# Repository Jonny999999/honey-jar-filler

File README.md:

# honey-jar-filler

Semi-automatic **weight-based honey jar filler** with a **jar carousel/magazine** and a
**servo-actuated honey gate**. A load cell weighs each jar in real time while the
firmware modulates the gate to hit a target fill mass.

This repository holds the complete build — **KiCad PCB**, **FreeCAD** mechanics, and
**ESP-IDF firmware** — plus the telemetry tooling used to capture and analyse fills.
The machine is also the subject of a **bachelor thesis** that evaluates several
**dosing strategies** for accurately dispensing a viscous, drifting medium (honey);
see [Dosing strategies](#dosing-strategies).

*System overview (CAD): pressurised bucket on the stand, the servo-actuated gate, and
the carousel base housing the control board and load cell, with a jar in position.*

*Left: the custom control board, fully populated. Right: I/O bring-up with all
peripherals connected.*

## Repo contents
- `pcb_honey-jar-filler/` — KiCad project (schematic, PCB, exports)
- `cad/` — FreeCAD parts, 3D models, full assembly
- `firmware_honey-jar-filler/` — ESP32 firmware (ESP-IDF)
- `tools/telemetry/` — host-side capture, run-splitting, and plotting tools
- `doc/` — build photos and notes

## Features (PCB / system)
- Load cell input (HX711) for weight-based dosing
- UI: rotary encoder, 2× buttons, LEDs, OLED display (I²C)
- Actuation: servo interface for honey gate; motor output for carousel
- Optional outputs: heater control, tank pressurization valve
- Power: 12–40 V input, 5 V buck (logic), adjustable 4–9 V rail (servo)

## Dosing strategies
Dosing honey accurately is hard: there is a **dead time** of several seconds between
moving the gate and seeing the weight respond, the flow **keeps dripping after the
gate closes**, the gate→flow relationship is **nonlinear**, and disturbances
(viscosity, temperature, falling bucket level) **drift within and between fills**.
Fixed thresholds therefore cannot stay optimal, which is what motivates the strategy
comparison at the heart of the thesis.

The firmware implements the strategies as interchangeable modules
(`firmware_honey-jar-filler/components/filler/`), selectable from the OLED menu:

- **heuristic** — fixed two-stage thresholds; the simple baseline.
- **adaptive-heuristic** — the same fill sequence, but dead time, post-close drip and
  fill rates are learned between fills, so it converges after a jar or two.
- **flow-cascade** — a control-based approach: an outer deceleration rate profile
  (feed-forward trajectory) feeding an inner PI rate loop with an online-identified
  affine plant model and Smith-predictor dead-time compensation.
- **manual** / **sequence** — encoder-driven and scripted modes, used for bring-up and
  for capturing clean reference runs.

## Roadmap / ideas
- Rotary carousel automation (indexing, run/stop with braking)
- Outlet warming (silicone band / water jacket)
- Jar presence detection
- Web UI / profiles / batch counter

## Schematic + layout preview
<p align="center">

</p>

## Firmware build (ESP-IDF)
- Install ESP-IDF **v5.5.1** and export its environment (`. ./export.sh`).
- Enter the firmware project:
```bash
cd firmware_honey-jar-filler
```
- Set the target and build:
```bash
idf.py set-target esp32
idf.py build
```
- No separate "install components" step is needed — `idf.py build` auto-fetches
  the managed components listed in `main/idf_component.yml` (esp-idf-lib hx711/
  encoder, ssd1306, servo, led_strip) into `managed_components/` on first run.
  `managed_components/` and `build/` are gitignored and regenerated per machine.
- `dependencies.lock` **is** committed and pins exact component versions — do
  not delete it. Some `idf_component.yml` entries use unbounded ranges (e.g.
  `esp-idf-lib/hx711: '*'`), and upstream has shipped breaking API changes
  under those ranges before (`esp-idf-lib/encoder` v2.0.0 rewrote the whole
  API); without the lock file, a fresh clone can silently resolve to an
  incompatible version and fail to compile.
- Flash and monitor (adjust serial port as needed):
```bash
idf.py -p /dev/ttyUSB0 flash monitor
```

## Firmware presets
- Runtime parameters are still defined centrally in `firmware_honey-jar-filler/components/app/app_params_def.h`.
- Each parameter there has one baseline default plus metadata such as min/max/step, UI text, and a scope:
  `APP_PARAM_SCOPE_PRESET` for recipe-specific values and `APP_PARAM_SCOPE_MACHINE` for shared machine settings.
- Built-in preset names and their default overrides live in `firmware_honey-jar-filler/components/app/app.c`.
  These preset defaults only override recipe-scoped fields; they do not duplicate the full parameter list.
- NVS stores shared machine settings separately from editable preset values:
  `machine_v1` for shared settings and `presets_v1` for preset-specific values.
- At boot, the active runtime config is rebuilt from baseline defaults + selected preset defaults + persisted machine settings + persisted preset values.

## Telemetry tools
- Structured telemetry is emitted on the normal UART console with a `TEL ` prefix and JSON payload.
- Normal ESP logs and machine telemetry therefore share one serial stream, but the telemetry lines can be split cleanly on the host.
- The intended workflow is:
  1. capture a session from UART
  2. keep the full console log for debugging
  3. store telemetry separately as NDJSON
  4. split runs and generate thesis figures from those files

Current script layout:
- `tools/telemetry/telemetry_tui.py`
  Recommended interactive wrapper / TUI entrypoint. Guides the user through
  capture, split, and plotting with session discovery, defaults, and command
  previews, while still calling the underlying scripts directly.
- `tools/telemetry/src/`
  Internal shared helpers for the telemetry scripts. Not intended to be run
  directly.
- `tools/telemetry/capture.py`
  Fully usable serial capture tool. Replaces the basic `idf.py monitor` workflow for experiment sessions and shows a live status line with telemetry counters.
- `tools/telemetry/split_runs.py`
  Offline splitter that converts one captured session into per-fill NDJSON files.
  It detects jar filling windows from `state=FILL`, adds configurable pre/post context,
  and writes `fills/index.json` plus `fill_0001.ndjson`, `fill_0002.ndjson`, ...
- `tools/telemetry/plot_runs.py`
  Offline chart exporter for thesis figures. It writes both a plain LaTeX-ready
  chart and a debug variant with metadata, based on fill mass, gate percentage,
  and FSM state overlays.
- `tools/telemetry/strategy_compare.py`
  Cross-strategy comparison charts (accuracy point clouds, speed–accuracy
  trade-off, throughput) for the thesis' strategy-comparison chapter. Reads each
  session's per-fill summaries and is explicit about which runs are a controlled
  comparison and which are only indicative.
- `tools/telemetry/cascade_analyze.py`
  Diagnostics for the flow-cascade strategy: per-fill plant-model estimate
  (gain/onset/lag) beside an offline ground-truth fit, to spot a diverging
  identifier at a glance.

Session capture output:
- `data/telemetry/<session>/session.log`
  Full serial console output, including normal ESP logs and raw `TEL` lines.
- `data/telemetry/<session>/telemetry.ndjson`
  Only telemetry payload lines, one JSON object per line.
- `data/telemetry/<session>/runs/run_0001.ndjson`
  Per-run telemetry files created live from `run_start` / `run_end` events, including configurable pre/post context.
- `data/telemetry/<session>/fills/index.json`
  Offline manifest of detected jar-fill windows with timing, preset, and parameter metadata.
- `data/telemetry/<session>/fills/fill_0001.ndjson`
  One offline per-fill telemetry slice intended for plotting and later comparison.
- `data/telemetry/<session>/session_meta.json`
  Port, baud rate, and capture timing settings.

Example capture usage:
```bash
python3 tools/telemetry/capture.py --port /dev/ttyUSB0 --baud 115200
```

Recommended interactive workflow:
```bash
python3 tools/telemetry/telemetry_tui.py
```

Example offline workflow:
```bash
python3 tools/telemetry/split_runs.py data/telemetry/2026.06.12_11:39-x-test --force
python3 tools/telemetry/plot_runs.py data/telemetry/2026.06.12_11:39-x-test/fills --list
python3 tools/telemetry/plot_runs.py data/telemetry/2026.06.12_11:39-x-test/fills --fills 1,3 --format pdf --format svg
```

Useful options:
- `--show-tel`
  Also print the `TEL` lines in the terminal instead of only saving them to files.
- `--pre-run-ms 2000 --post-run-ms 2000`
  Keep more telemetry context around each detected run.
- `--session-name my-test`
  Add a readable suffix after the timestamp, for example
  `2026.06.07_22:30-x-my-test`.

Goal of this tooling:
- keep experiment data self-describing and reproducible
- avoid manually filtering UART logs after each test
- support later batch plotting to vector PDF/SVG figures for the thesis
- preserve enough event context to compare different presets and control strategies cleanly
- make it obvious during capture that the custom telemetry tool is running, not plain `idf.py monitor`

## Wiring (servo mount DIN cable)
The cable with 15-pin DIN connector from the base assembly to the servo mount carries OLED, encoder, and servo signals + power.

OLED:
- green: GND
- red: 3V3
- orange: SDA
- yellow: SCL

Encoder:
- gray: SW
- blue: B
- light-green: A

Servo:
- brown, gray-brown, pink: 8V
- gray-black, black, white: GND
- purple: PWM

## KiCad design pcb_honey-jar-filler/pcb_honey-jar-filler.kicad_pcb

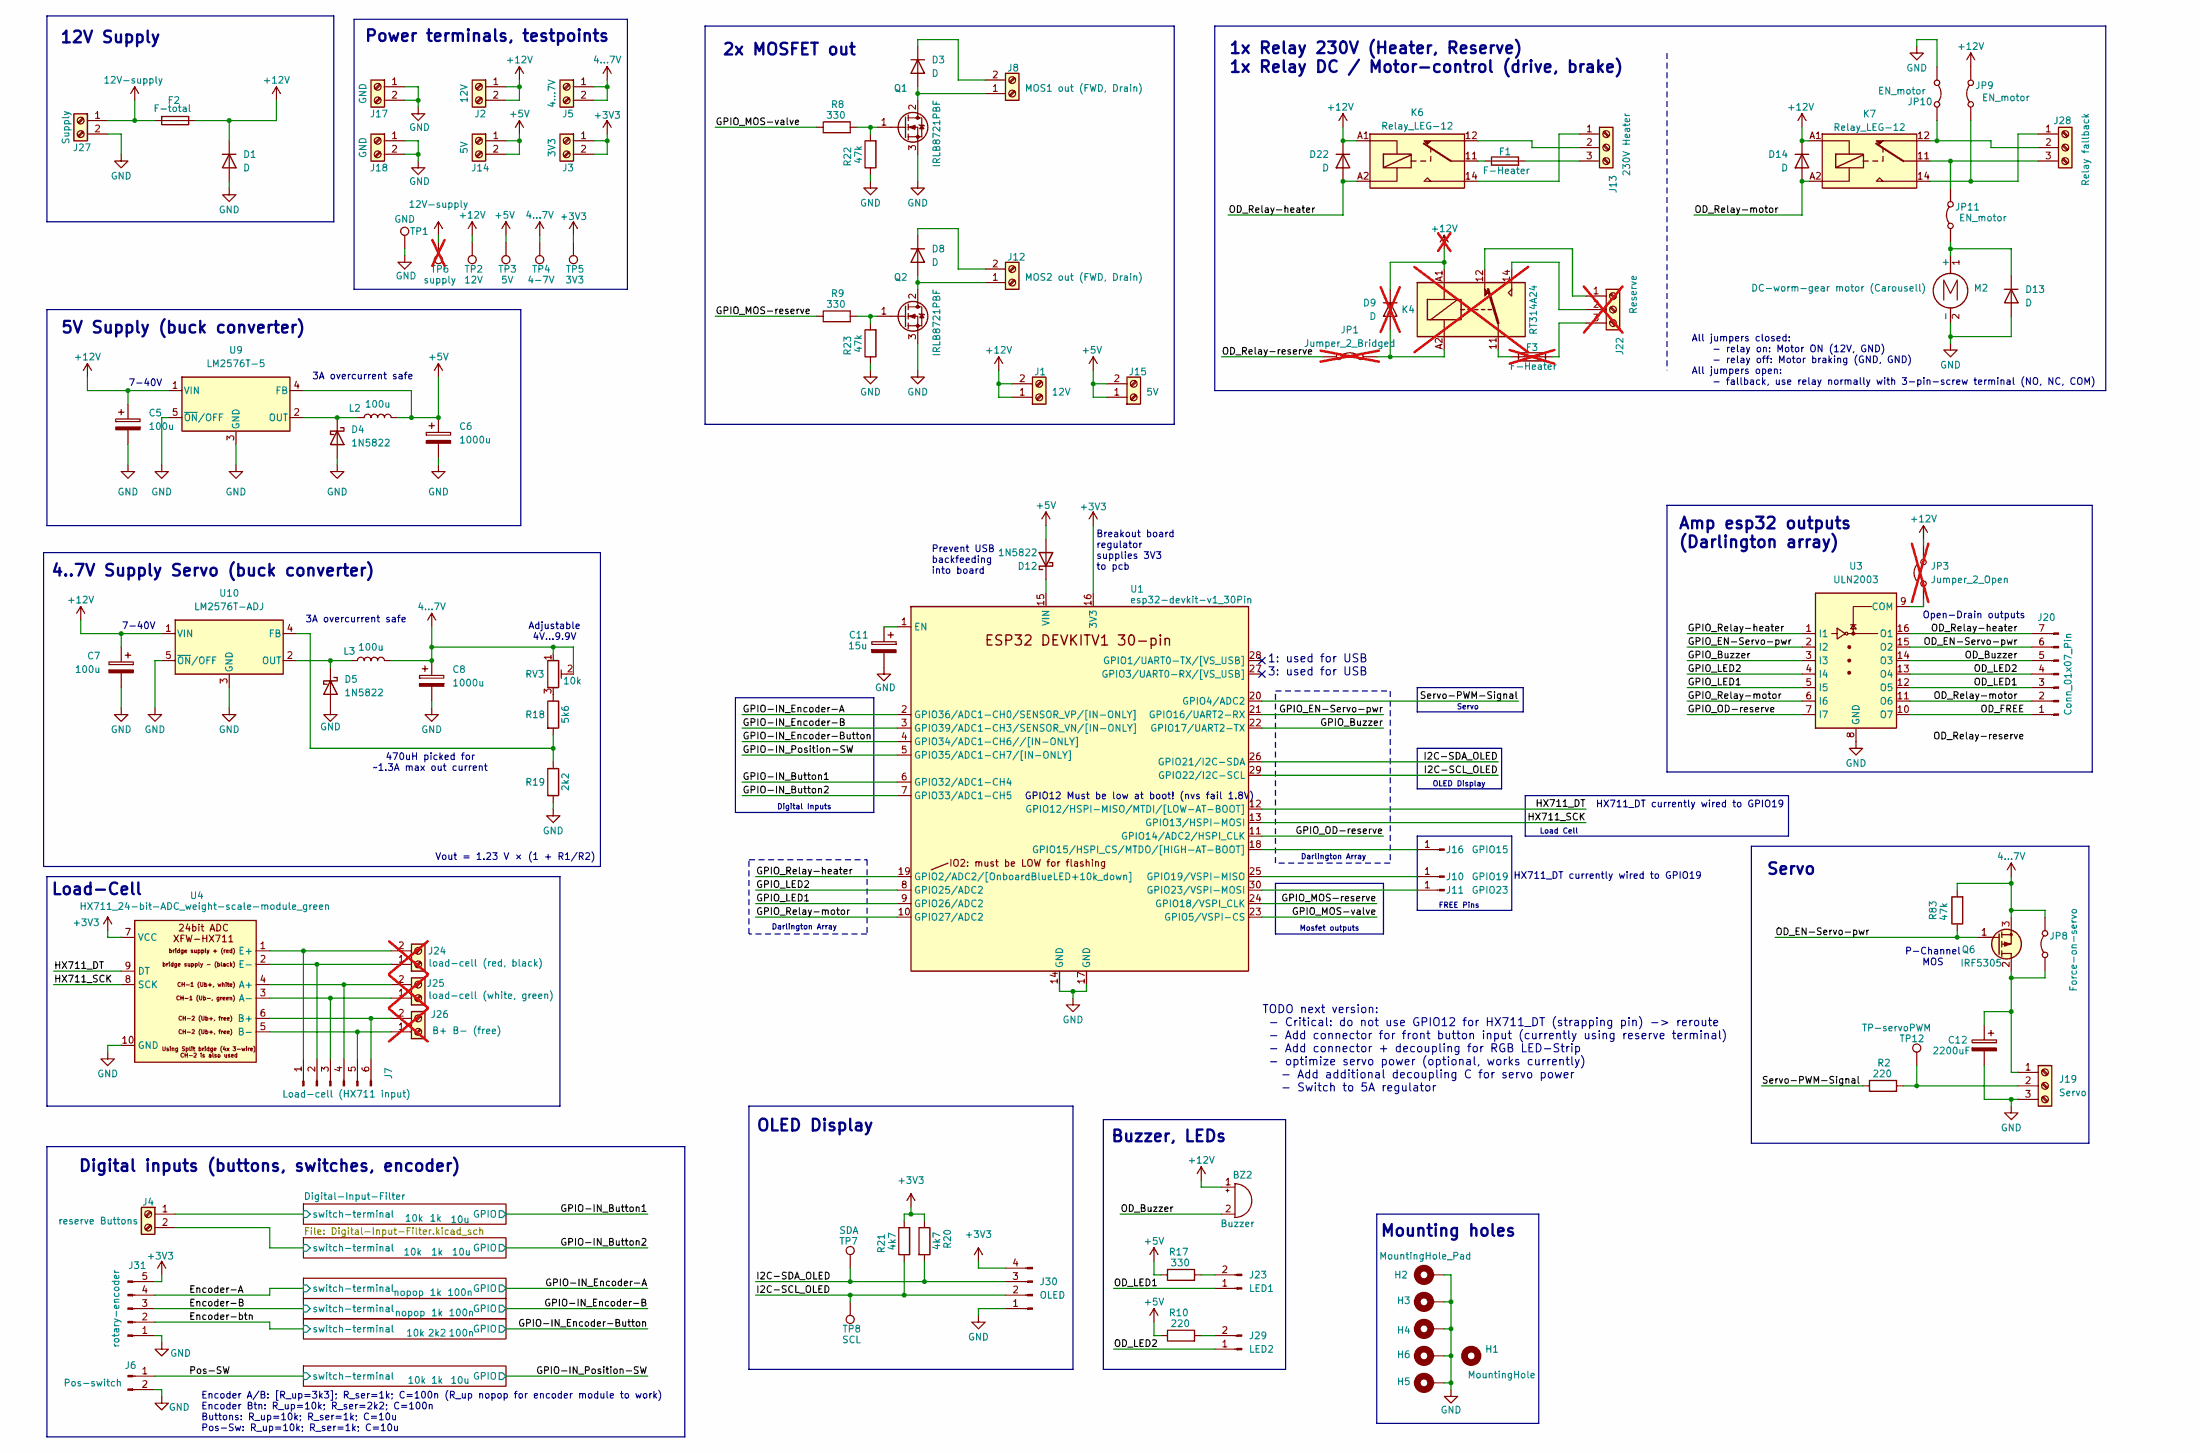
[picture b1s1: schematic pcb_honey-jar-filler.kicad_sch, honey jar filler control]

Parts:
BZ2: Buzzer; Buzzer_TDK_PS1240P02BT_D12.2mm_H6.5mm
C5, C7: 100u; CP_Radial_D8.0mm_P5.00mm
C6, C8: 1000u; CP_Radial_D10.0mm_P5.00mm
C11: 15u; CP_Radial_D6.3mm_P2.50mm
C12: 2200uF; CP_Radial_D10.0mm_P5.00mm
D1, D3, D8, D22: D; D_T-1_P12.70mm_Horizontal
D4, D12: 1N5822; D_DO-201AD_P15.24mm_Horizontal
D5: 1N5822; D_DO-201AE_P5.08mm_Vertical_AnodeUp
D9: D; D_T-1_P12.70mm_Horizontal; not fitted
D13, D14: D; D_T-1_P2.54mm_Vertical_KathodeUp
F1: F-Heater; Fuseholder_Cylinder-5x20mm_Stelvio-Kontek_PTF78_Horizontal_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
F2: F-total; Fuseholder_Automotive-Mini_Fuse11x4x16_Footprint15x5_Inline
F3: F-Heater; Fuseholder_Automotive-Mini_Fuse11x4x16_Footprint15x5_Inline; not fitted
H1: MountingHole; MountingHole_3mm
H2, H3, H4, H5, H6: MountingHole_Pad; MountingHole_2.2mm_NPTH-with-pad_DRC-clearance-error
J1, J2: 12V; ScrewTerminal_P5mm_2Pin_FP10x8
J3: 3V3; ScrewTerminal_P5mm_2Pin_FP10x8
J4: reserve Buttons; ScrewTerminal_P3.5mm_2Pin_FP7x7
J5: 4...7V; ScrewTerminal_P5mm_2Pin_FP10x8
J6: Pos-switch; JST_XH_B2B-XH-A_1x02_P2.50mm_Vertical
J7: Load-cell (HX711 input); JST_XH_B6B-XH-A_1x06_P2.50mm_Vertical
J8: MOS1 out (FWD, Drain); ScrewTerminal_P5mm_2Pin_FP10x8
J10: GPIO19; PinHeader_1x01_P2.54mm_Vertical
J11: GPIO23; PinHeader_1x01_P2.54mm_Vertical
J12: MOS2 out (FWD, Drain); ScrewTerminal_P5mm_2Pin_FP10x8
J13: 230V Heater; ScrewTerminal_P5mm_3Pin_FP15x8
J14, J15: 5V; ScrewTerminal_P5mm_2Pin_FP10x8
J16: GPIO15; PinHeader_1x01_P2.54mm_Vertical
J17, J18: GND; ScrewTerminal_P5mm_2Pin_FP10x8
J19: Servo; ScrewTerminal_P5mm_3Pin_FP15x8
J20: Conn_01x07_Pin; PinHeader_1x07_P2.54mm_Vertical
J22: Reserve; ScrewTerminal_P5mm_3Pin_FP15x8; not fitted
J23: LED1; JST_XH_B2B-XH-A_1x02_P2.50mm_Vertical
J24: load-cell (red, black); ScrewTerminal_P3.5mm_2Pin_FP7x7; not fitted
J25: load-cell (white, green); ScrewTerminal_P3.5mm_2Pin_FP7x7; not fitted
J26: B+ B- (free); ScrewTerminal_P3.5mm_2Pin_FP7x7; not fitted
J27: Supply; ScrewTerminal_P5mm_2Pin_FP10x8
J28: Relay fallback; ScrewTerminal_P5mm_3Pin_FP15x8
J29: LED2; JST_XH_B2B-XH-A_1x02_P2.50mm_Vertical
J30: OLED; JST_XH_B4B-XH-A_1x04_P2.50mm_Vertical
J31: rotary-encoder; JST_XH_B5B-XH-A_1x05_P2.50mm_Vertical
JP1: Jumper_2_Bridged; PinHeader_1x02_P2.54mm_Vertical; not fitted
JP3: Jumper_2_Open; PinHeader_1x02_P2.54mm_Vertical; not fitted
JP8: Force-on-servo; PinHeader_1x02_P2.54mm_Vertical
JP9, JP10, JP11: EN_motor; PinHeader_1x02_P2.54mm_Vertical
K4: RT314A24; Relay_SPDT_Schrack-RT1-16A-FormC_RM5mm; not fitted
K6, K7: Relay_LEG-12; Relay_LEG-xxF
L2, L3: 100u; L_Toroid_Vertical_L14.0mm_W6.3mm_P4.57mm_Pulse_A
M2: DC-worm-gear motor (Carousell); ScrewTerminal_P5mm_2Pin_FP10x8
Q1, Q2: IRLB8721PBF; TO-220-3_Vertical
Q6: IRF5305; TO-220-3_Vertical
R2, R10: 220; R_Axial_DIN0207_L6.3mm_D2.5mm_P10.16mm_Horizontal
R8, R9, R17: 330; R_Axial_DIN0207_L6.3mm_D2.5mm_P10.16mm_Horizontal
R18: 5k6; R_Axial_DIN0207_L6.3mm_D2.5mm_P10.16mm_Horizontal
R19: 2k2; R_Axial_DIN0207_L6.3mm_D2.5mm_P10.16mm_Horizontal
R20: 4k7; R_Axial_DIN0204_L3.6mm_D1.6mm_P2.54mm_Vertical
R21: 4k7; R_Axial_DIN0207_L6.3mm_D2.5mm_P10.16mm_Horizontal
R22, R23, R83: 47k; R_Axial_DIN0207_L6.3mm_D2.5mm_P10.16mm_Horizontal
RV3: 10k; Potentiometer_Piher_PT-10-V10_Vertical
TP1: GND; PinHeader_1x01_P2.54mm_Vertical
TP2: 12V; PinHeader_1x01_P2.54mm_Vertical
TP3: 5V; PinHeader_1x01_P2.54mm_Vertical
TP4: 4-7V; PinHeader_1x01_P2.54mm_Vertical
TP5: 3V3; PinHeader_1x01_P2.54mm_Vertical
TP6: supply; PinHeader_1x01_P2.54mm_Vertical; not fitted
TP7: SDA; PinHeader_1x01_P2.54mm_Vertical
TP8: SCL; PinHeader_1x01_P2.54mm_Vertical
TP12: TP-servoPWM; PinHeader_1x01_P2.54mm_Vertical
U1: esp32-devkit-v1_30Pin
U3: ULN2003; DIP-16_W7.62mm_LongPads
U4: HX711_24-bit-ADC_weight-scale-module_green
U9: LM2576T-5; TO-220-5_P3.4x3.7mm_StaggerOdd_Lead3.8mm_Vertical
U10: LM2576T-ADJ; TO-220-5_P3.4x3.7mm_StaggerOdd_Lead3.8mm_Vertical

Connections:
4...7V: C8.1, J5.1, J5.2, JP8.2 (B), L3.2, Q6.3 (S), R83.2, RV3.1, RV3.2, TP4.1
12V-supply: F2.2, J27.1, TP6.1
+3V3: J3.1, J3.2, J30.4, J31.5, R20.1, R21.2, TP5.1, U1.16 (3V3), U4.7 (VCC); also elsewhere on the board
+5V: C6.1, D12.2 (A), J14.1, J14.2, J15.1, J15.2, L2.2, R10.1, R17.1, TP3.1, U9.4 (FB)
+12V: BZ2.1 (+), C5.1, C7.1, D1.1 (K), D9.1 (K), D14.1 (K), D22.1 (K), F2.1, J1.1, J1.2, J2.1, J2.2, JP3.2 (B), JP9.2 (B), K4.A1, K6.A1, K7.A1, TP2.1, U9.1 (VIN), U10.1 (VIN)
/Digital-Input-Filter1/switch-terminal: J4.2; also elsewhere on the board
/Digital-Input-Filter/switch-terminal: J4.1; also elsewhere on the board
/Encoder-A: J31.4; also elsewhere on the board
/Encoder-B: J31.3; also elsewhere on the board
/Encoder-btn: J31.2; also elsewhere on the board
/GPIO-IN_Button1: U1.6 (GPIO32/ADC1-CH4); also elsewhere on the board
/GPIO-IN_Button2: U1.7 (GPIO33/ADC1-CH5); also elsewhere on the board
/GPIO-IN_Encoder-A: U1.2 (GPIO36/ADC1-CH0/SENSOR_VP/[IN-ONLY]); also elsewhere on the board
/GPIO-IN_Encoder-B: U1.3 (GPIO39/ADC1-CH3/SENSOR_VN/[IN-ONLY]); also elsewhere on the board
/GPIO-IN_Encoder-Button: U1.4 (GPIO34/ADC1-CH6//[IN-ONLY]); also elsewhere on the board
/GPIO-IN_Position-SW: U1.5 (GPIO35/ADC1-CH7/[IN-ONLY]); also elsewhere on the board
/GPIO_Buzzer: U1.22 (GPIO17/UART2-TX), U3.3 (I3)
/GPIO_EN-Servo-pwr: U1.21 (GPIO16/UART2-RX), U3.2 (I2)
/GPIO_LED1: U1.9 (GPIO26/ADC2), U3.5 (I5)
/GPIO_LED2: U1.8 (GPIO25/ADC2), U3.4 (I4)
/GPIO_MOS-reserve: R9.1, U1.24 (GPIO18/VSPI_CLK)
/GPIO_MOS-valve: R8.1, U1.23 (GPIO5/VSPI-CS)
/GPIO_OD-reserve: U1.11 (GPIO14/ADC2/HSPI_CLK), U3.7 (I7)
/GPIO_Relay-heater: U1.19 (GPIO2/ADC2/[OnboardBlueLED+10k_down]), U3.1 (I1)
/GPIO_Relay-motor: U1.10 (GPIO27/ADC2), U3.6 (I6)
/HX711_DT: U1.12 (GPIO12/HSPI-MISO/MTDI/[LOW-AT-BOOT]), U4.9 (DT)
/HX711_SCK: U1.13 (GPIO13/HSPI-MOSI), U4.8 (SCK)
/I2C-SCL_OLED: J30.2, R21.1, TP8.1, U1.29 (GPIO22/I2C-SCL)
/I2C-SDA_OLED: J30.3, R20.2, TP7.1, U1.26 (GPIO21/I2C-SDA)
/OD_Buzzer: BZ2.2 (-), J20.5, U3.14 (O3)
/OD_EN-Servo-pwr: J20.6, Q6.1 (G), R83.1, U3.15 (O2)
/OD_FREE: J20.1, U3.10 (O7)
/OD_LED1: J20.3, J23.1, U3.12 (O5)
/OD_LED2: J20.4, J29.1, U3.13 (O4)
/OD_Relay-heater: D22.2 (A), J20.7, K6.A2, U3.16 (O1)
/OD_Relay-motor: D14.2 (A), J20.2, K7.A2, U3.11 (O6)
/Pos-SW: J6.1; also elsewhere on the board
/Servo-PWM-Signal: R2.1, U1.20 (GPIO4/ADC2)
GND: C5.2, C6.2, C7.2, C8.2, C11.2, C12.2, D1.2 (A), D4.2 (A), D5.2 (A), D13.2 (A), H2.1, H3.1, H4.1, H5.1, H6.1, J6.2, J17.1, J17.2, J18.1, J18.2, J19.3, J27.2, J30.1, J31.1, JP10.1 (A), M2.2 (-), Q1.3 (S), Q2.3 (S), R19.2, R22.1, R23.1, TP1.1, U1.14 (GND), U1.17 (GND), U3.8 (GND), U4.10 (GND), U9.3 (GND), U9.5 (~ON/OFF), U10.3 (GND), U10.5 (~ON/OFF); also elsewhere on the board
unnamed: D3.2 (A), J8.1, Q1.2 (D)
unnamed: D3.1 (K), J8.2
unnamed: D4.1 (K), L2.1, U9.2 (OUT)
unnamed: D5.1 (K), L3.1, U10.2 (OUT)
unnamed: D8.2 (A), J12.1, Q2.2 (D)
unnamed: D8.1 (K), J12.2
unnamed: D9.2 (A), JP1.2 (B), K4.A2
unnamed: D12.1 (K), U1.15 (VIN)
unnamed: D13.1 (K), JP11.1 (A), M2.1 (+)
unnamed: F1.1, K6.11
unnamed: F3.1, K4.11
unnamed: F3.2, J22.3
unnamed: J7.1, J24.2, U4.1 (E+)
unnamed: J7.2, J24.1, U4.2 (E-)
unnamed: J7.3, J25.1, U4.3 (A-)
unnamed: J7.4, J25.2, U4.4 (A+)
unnamed: J7.5, J26.1, U4.5 (B-)
unnamed: J7.6, J26.2, U4.6 (B+)
unnamed: J10.1, U1.25 (GPIO19/VSPI-MISO)
unnamed: J11.1, U1.30 (GPIO23/VSPI-MOSI)
unnamed: J13.1, K6.14
unnamed: J13.2, K6.12
unnamed: F1.2, J13.3
unnamed: J16.1, U1.18 (GPIO15/HSPI_CS/MTDO/[HIGH-AT-BOOT])
unnamed: C12.1, J19.1, JP8.1 (A), Q6.2 (D)
unnamed: J19.2, R2.2, TP12.1
unnamed: J22.1, K4.12
unnamed: J22.2, K4.14
unnamed: J23.2, R17.2
unnamed: J28.1, JP9.1 (A), K7.14
unnamed: J28.2, JP10.2 (B), K7.12
unnamed: J28.3, JP11.2 (B), K7.11
unnamed: J29.2, R10.2
unnamed: Q1.1 (G), R8.2, R22.2
unnamed: Q2.1 (G), R9.2, R23.2
unnamed: R18.1, RV3.3
unnamed: C11.1, U1.1 (EN)
unnamed: JP3.1 (A), U3.9 (COM)
unnamed: R18.2, R19.1, U10.4 (FB)

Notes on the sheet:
470uH picked for ~1.3A max out current
3A overcurrent safe
Darlington Array
Digital Inputs
2x MOSFET out
5V Supply (buck converter)
GPIO12 Must be low at boot! (nvs fail 1.8V)
Power terminals, testpoints
Adjustable 4V...9.9V
TODO next version: - Critical: do not use GPIO12 for HX711_DT (strapping pin) -> reroute - Add connector for front button input (currently using reserve terminal) - Add connector + decoupling for RGB LED-Strip - optimize servo power (optional, works currently) - Add additional decoupling C for serv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
Encoder A/B: [R_up=3k3]; R_ser=1k; C=100n (R_up nopop for encoder module to work) Encoder Btn: R_up=10k; R_ser=2k2; C=100n Buttons: R_up=10k; R_ser=1k; C=10u Pos-Sw: R_up=10k; R_ser=1k; C=10u
Buzzer, LEDs
OLED Display
Breakout board regulator supplies 3V3 to pcb
Digital inputs (buttons, switches, encoder)
Load Cell
Mosfet outputs
4..7V Supply Servo (buck converter)
HX711_DT currently wired to GPIO19
1: used for USB 3: used for USB
Load-Cell
P-Channel MOS
1x Relay 230V (Heater, Reserve) 1x Relay DC / Motor-control (drive, brake)
Mounting holes
Open-Drain outputs
Vout = 1.23 V × (1 + R1/R2)
Amp esp32 outputs (Darlington array)
Servo
7-40V
12V Supply
Prevent USB backfeeding into board
FREE Pins
All jumpers closed: - relay on: Motor ON (12V, GND) - relay off: Motor braking (GND, GND) All jumpers open: - fallback, use relay normally with 3-pin-screw terminal (NO, NC, COM)

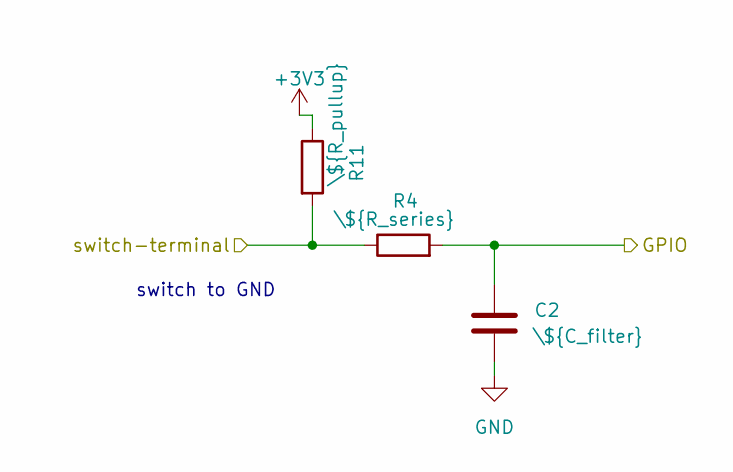
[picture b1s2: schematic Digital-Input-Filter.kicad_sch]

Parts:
C2: \${C_filter}; C_DualType__Disc-7.0x2.5mm-P5mm__Elko-D5mm-P2.5mm
R4: \${R_series}; R_Axial_DIN0207_L6.3mm_D2.5mm_P10.16mm_Horizontal
R11: \${R_pullup}; R_Axial_DIN0207_L6.3mm_D2.5mm_P10.16mm_Horizontal

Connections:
+3V3: R11.1; also elsewhere on the board
/Digital-Input-Filter/switch-terminal: R4.1, R11.2; also elsewhere on the board
/GPIO-IN_Button1: C2.1, R4.2; also elsewhere on the board
GND: C2.2; also elsewhere on the board

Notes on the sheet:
switch to GND

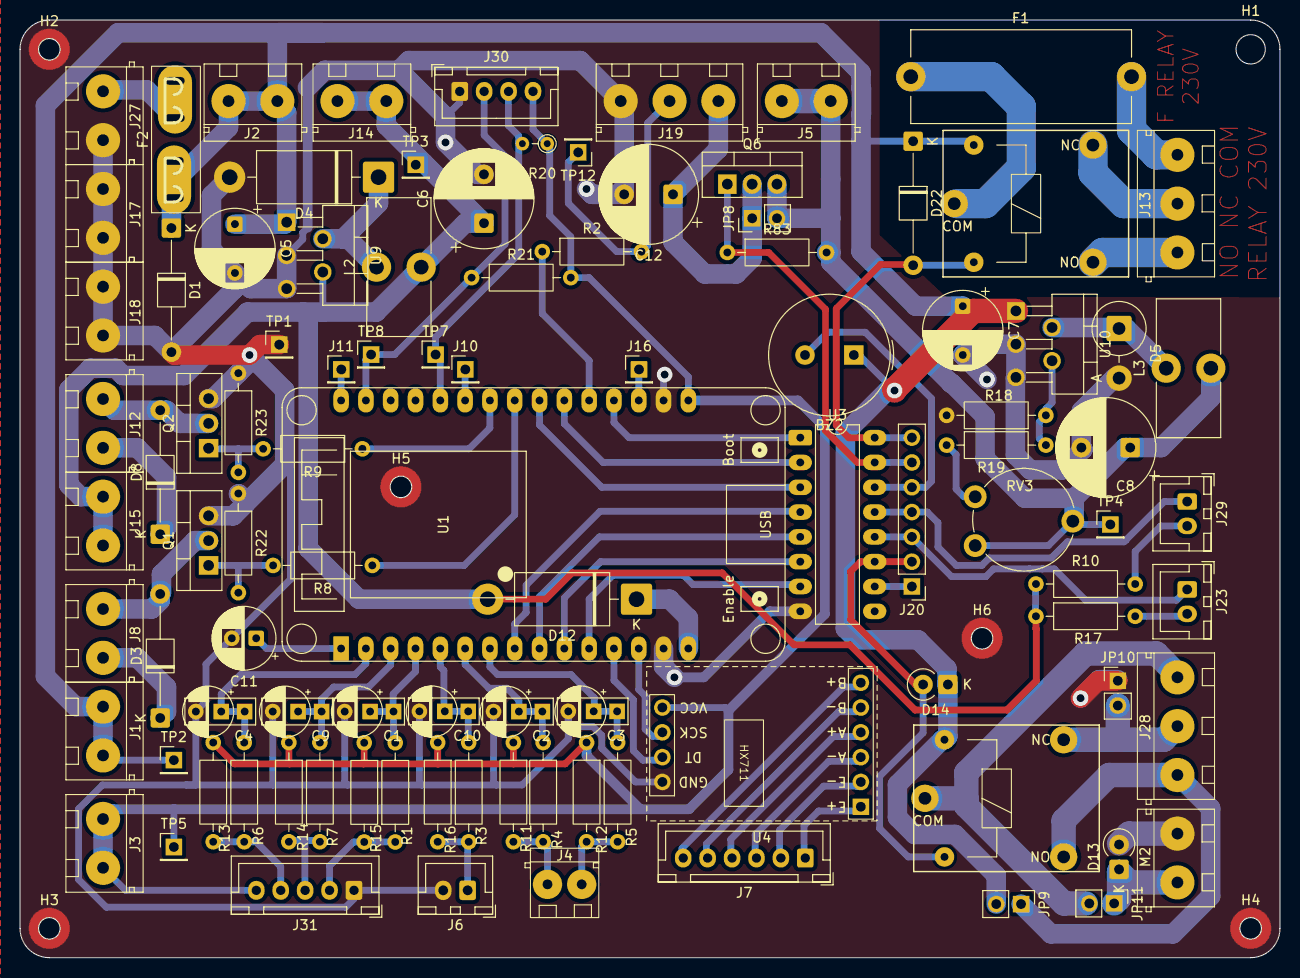
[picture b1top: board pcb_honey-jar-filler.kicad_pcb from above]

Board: 2 copper layers, 129.0 x 96.0 mm, 105 parts (0 on the bottom side), 72 nets.

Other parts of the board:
C1, C4, C9: \100n; C_DualType__Disc-7.0x2.5mm-P5mm__Elko-D5mm-P2.5mm
C3, C10: \10u; C_DualType__Disc-7.0x2.5mm-P5mm__Elko-D5mm-P2.5mm
R1: \2k2; R_Axial_DIN0207_L6.3mm_D2.5mm_P10.16mm_Horizontal
R3, R5, R6, R7: \1k; R_Axial_DIN0207_L6.3mm_D2.5mm_P10.16mm_Horizontal
R12, R15, R16: \10k; R_Axial_DIN0207_L6.3mm_D2.5mm_P10.16mm_Horizontal
R13, R14: \nopop; R_Axial_DIN0207_L6.3mm_D2.5mm_P10.16mm_Horizontal

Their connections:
+3V3: R12.1, R13.1, R14.1, R15.1, R16.1; also elsewhere on the board
/Digital-Input-Filter1/switch-terminal: R5.1, R12.2; also elsewhere on the board
/Encoder-A: R6.1, R13.2; also elsewhere on the board
/Encoder-B: R7.1, R14.2; also elsewhere on the board
/Encoder-btn: R1.1, R15.2; also elsewhere on the board
/GPIO-IN_Button2: C3.1, R5.2; also elsewhere on the board
/GPIO-IN_Encoder-A: C4.1, R6.2; also elsewhere on the board
/GPIO-IN_Encoder-B: C9.1, R7.2; also elsewhere on the board
/GPIO-IN_Encoder-Button: C1.1, R1.2; also elsewhere on the board
/GPIO-IN_Position-SW: C10.1, R3.2; also elsewhere on the board
/Pos-SW: R3.1, R16.2; also elsewhere on the board
GND: C1.2, C3.2, C4.2, C9.2, C10.2; also elsewhere on the board

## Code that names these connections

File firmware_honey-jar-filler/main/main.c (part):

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        | BIT64(CONFIG_MOS_RESERVE_GPIO)
        | BIT64(CONFIG_OPEN_DRAIN_RESERVE_GPIO) // NOTE: currently push-pull
        | BIT64(CONFIG_RELAY_MOTOR_GPIO)
        | BIT64(CONFIG_RELAY_230V_GPIO)         // GPIO2 kept LOW at boot
        //| BIT64(CONFIG_SERVO_PWM_GPIO)          // LEDC will re-own later
        | BIT64(CONFIG_SERVO_ENABLE_GPIO);

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
    // Describe encoder pins (button optional)
    static rotary_encoder_t enc = {
        .pin_a  = CONFIG_ENCODER_A_GPIO,      // e.g. GPIO36
        .pin_b  = CONFIG_ENCODER_B_GPIO,      // e.g. GPIO39
        .pin_btn= CONFIG_ENCODER_SW_GPIO,     // e.g. GPIO34, or >=GPIO_NUM_MAX if none
    };
    // Register encoder
    ESP_ERROR_CHECK(rotary_encoder_add(&enc));
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
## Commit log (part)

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2025-10-28 init - FreeCAD assembly of concept functional
2025-10-29 Add kicad project - base components designed (schematic)
2025-11-02 pcb: arrange parts, re-assign, add servo-cutoff
2025-11-03 pcb: initial routing complete, some terminals -> JST connector
2025-11-03 pcb: Add text, testpoints, i2c-pull, Cleanup - DRC-pass
2025-11-03 pcb: Add MOS pulldowns, Schematic cleanup
2025-11-04 Add pcb2gcode script + configs (copy from gate-project), Adjust
2025-11-08 pcb: Fix invalid text
2025-11-08 Add exports + README, Adjust pcb2gcode configs
2025-11-08 pcb: Arrange fab text, Annotate for soldering, Fix "PWM" text
2025-11-09 Create new esp-idf 5.5.1 project (blink example)
2025-11-09 Add config.h with gpio assignments, Add iotest - digital IO's work
2025-11-10 Add HX711 driver (lib driver+custom wrapper) - load cell works
2025-11-10 Optimize HX711 wrapper (poll-task + readout-queue, store calib in nvs, mutex)
2025-11-10 pcb: Update actually soldered filter R values (use sub-sheet parameters)
2025-11-10 Add support for rotary-encoder - works, logs event queue
2025-11-11 Add support for oled-display - works, shows weight+encoder events
2025-11-11 Add support for servo-motor - works, cycles positions
2025-11-27 Update README (install instructions, photos)
2025-12-02 CAD: Add motor-adapter, Optimize index
2025-12-13 CAD: Create base (wip), Add pcb, power-supply
2025-12-15 CAD: Add motor-mount, levers, servo
2025-12-21 CAD: Add load-cell mount, pcb mount to base (printed)
2025-12-21 CAD: Adjust index (switch to magnets), Add slide-plate screws + reed mount
2025-12-23 CAD: Add ui-box to servo-mount
2025-12-23 CAD: Add housing cylinder / rim with connector mounts
2025-12-25 FW: Add tasks for testing the hardware (motor, servo, pos-switch) - hardware works
2025-12-25 CAD: Adjustments after first print: conn-clamp, display-clamp, weigh-plate mount
2025-12-25 FW: create custom components "app, gate, motor"
2025-12-25 FW: hx711 store and provide latest snapshot threadsafe (besides queue)
2025-12-27 CAD: Optimize disk, slide-plate, weigh-plate; Add adjustable reed-mount
2025-12-27 CAD - base: apply fixes, add led-strip, loadCell-guard, cable guide
2025-12-27 CAD - servo-mount: fix encoder, add lever-v2
2025-12-28 FW: Add servo-calibration-task, toggle-gate-task, Rework gate component (percentage + logging)
2025-12-28 CAD: Optimize disk, base, gate-interface (next version printed)
2025-12-28 FW: Add custom components fsm, ui - WIP crashes on calibration nvs store
2025-12-29 debug: Remove all code except nvs-init + hx711-calibration
2025-12-29 debug: remove hx711 code (bare init+write)
2025-12-29 debug: add option to test simple-write vs calibration, Add delay before write
2025-12-29 debug: add looped write action with count
2025-12-29 debug: Issue crash on nvs write located (strapping pin)
2025-12-29 CAD: base-ring adjust strip-angle, increase screw-dia
2025-12-29 Fix crash on nvs-write: Change H711 DT-pin (non strapping), Add notes to schematic + pcb
2025-12-29 FW: Optimize fsm (sequence, cleanup), Add new settings, versioning, logging to app.c
2025-12-29 FW: Add custom component buzzer, beep at encoder, beep on state change
2025-12-30 FW: Add support for RGB-LED-Strip (test task)
2025-12-30 FW: Add silent mode, led startup sequence, by-state led colors, Fix rotating too far
2025-12-30 FW: Add glass-weight compensation/tare, led loading animation, more params
2025-12-30 FW: Fix 'hx711_read_average failed' using other core and task priority
2025-12-30 FW: Ignore measurement spikes (sable for n), Fix servo oscillation / gate threshold not loosened at retry
2025-12-30 FW: Cleanup - simplify ui delay, Re-arrange app params + config
2025-12-31 CAD: Update assembly (re-create), adjust colors; DOC: Update README (screenshot, wiring)
2025-12-31 FW: Add meta to app params and centralize with macro definitions
2025-12-31 FW: Add settings menu for changing all params (oled + encoder)
2026-01-02 FW: Adjust app params, Fix dup code - generate struct typdef from param def
2026-01-02 FW: Optimize menu UX (wrap list, beeps, blink value, wrap desc)
2026-01-03 FW: Add menu entries: Gate angle calibration + run Scale calibration
2026-04-23 FW: Adjust param step-sizes, Add second dim section to led-strip animation
2026-04-23 FW: Allow param changes during active run (UI-task: Encoder + Display)
2026-04-23 FW: Change run end-logic for continuous operation (re-try slots, only stop when consecutive unavailable)
2026-04-30 FW: Refactor param loading (prepare for presets)
2026-04-30 FW: Add editable presets with shared machine settings and oled preset menu
2026-05-31 FW: Document config-presets, add comments
2026-06-01 FW: Fix scale readout invalid (calibrated flag was not set)
2026-06-01 FW: Optimize menu ux, Sync thick/thin preset actual tested parameters
2026-06-03 CAD: Add bucket-stand, Adjust all colors for thesis
2026-06-03 FW: Add telemetry component - queue, task, uart ndjson output
2026-06-04 FW: Add telemetry output for scale samples and fsm events
2026-06-04 FW: Add optional startup hw-fallbacks (disp+scale) and simulated scale reads for telemetry testing
2026-06-06 FW: Add run summary telemetry output
2026-06-06 FW: Add telemetry capture tooling (WIP) + document workflow
2026-06-11 TOOL: Add log level colors telemetry capture output, Optimize naming
2026-06-11 TOOL: Fix telemetry uart line interleaving, Add capture status-line
2026-06-11 TOOL: optimize capture script - live status panel, charting, startup/shutdown UX
2026-06-12 FW: Add fill_start metadata + scale/fsm timing to telemetry
2026-06-12 TOOL: Add scripts to split runs and plot charts
2026-06-12 TOOL: Add telemetry TUI wrapper script, Add state-bar to chart
2026-06-14 Split fill-process from machine fsm, Add support for different strategies (menu, structure...)
2026-06-14 FW: Add new fill strategy: adaptive-heuristic
2026-06-14 FW: Add new fill strategy: manual (encoder->gate, button->spin)
2026-06-14 FW/TOOL: Extend meta telemetry for all strategies + add to chart
2026-06-14 FW: adaptive strategy: Learn faster, simplify close-fully threshold, Fix manual mode
2026-06-14 FW: Add new fill strategy: flow-control
2026-06-15 FW: Fixes in adaptive strategy during actual test (min refill, longer timeout...)
2026-06-17 TOOL: Optimize chart plot, Fix splitting
2026-06-17 FW: Improve adaptive near-close learning, Add richer rate telemetry
2026-06-17 FW: Iimprove flow-control-strategy - start gates and add finish-trim learning
2026-06-18 TOOL: Fix broken layout in chart tool, Add summary-plots per session
